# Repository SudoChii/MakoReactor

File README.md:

# Mako Reactor

CAD-as-code for layered leverless ("hitbox" style) fight controllers.

Describe where the buttons go, and Mako Reactor gives you back a stack of flat
plates you can send to a laser cutter, router, or 3D printer.

```python
import makoreactor as mr
from affine import Affine
from cadquery import exporters

layout = mr.FgcLeverless()
layout.layout_affine = Affine.translation(0, -13)

stack = mr.f1CapMako1.set(
    width=mr.in2mm(11.8),
    height=mr.in2mm(5),
    hole_deltax=300,
    layout=layout,
)

for i, plate in enumerate(stack.generate()):
    exporters.export(plate.edges(">Z"), f"layer{i}.dxf")
```

Or from a shell:

```bash
python -m makoreactor --layout fgc --width 11.8 --height 5 -o build/
```

## Install

Everything is available from conda-forge, so a single environment file covers it:

```bash
# replace mamba with conda if you don't have mamba
mamba env create -f environment.yml
mamba activate mako

pip install -e .
```

If you'd rather use pip alone, `pip install -e .` pulls `cadquery`, `numpy`, and
`affine` from PyPI; CadQuery ships the OpenCascade binaries as wheels.

Check it works:

```bash
pytest
```

## How it fits together

### Layouts (`makoreactor/layouts.py`)

A `Layout` holds button centres grouped by hand and function — `left_homerow`,
`right_homerow`, `left_thumb`, `right_thumb`, `misc` — and one affine per group
placing it on the plate. `layout_affine` shifts the whole cluster at once.

| layout | buttons | notes |
| --- | --- | --- |
| `CircleCapLeverless` | 20 | smash layout, Frame 1 circular caps |
| `Gccmx` | 22 | as above plus home/share, mimics Crane's GCCMX |
| `SquareCapLeverless` | 20 | smash layout, square MX keycaps |
| `Mako1Hadoe` | 20 | as above, right-hand eight dropped onto the home row |
| `WideGc` | 18 | as `Gccmx`, two thumb buttons a hand, no left pinky |
| `FgcLeverless` | 15 | traditional fighting-game layout, one thumb button |
| `SanwaFgcLeverless` | 15 | as above, spread out for 24/30mm Sanwa buttons |
| `FgcPlus` | 16 | as above on the smash spacing, pinky and two thumbs a hand, all 24mm |

The eight action buttons sit in two rows 22mm apart. In the smash layouts the
*bottom* row lines up with the four directionals, so the fingers rest low and
reach up; `Mako1Hadoe` drops the whole cluster by that one row pitch so the
*top* row lands on the home row instead.

`WideGc` keeps the smash spacing and the right hand's eight, and changes the
other three groups. The stock thumbs are lopsided — two buttons on the left, a
five-button c-stick on the right — so it cuts the right cluster back to its
bottom two, the same pair the left thumb already has, and both thumbs end up
with the same reach. The centre is Crane's, inherited from `Gccmx`: a row of
three on a 20mm pitch where the stock layout has one button. The left hand
loses its pinky — the outermost of its four, the same button `FgcLeverless`
drops — leaving three directionals. Eighteen buttons.

Dropping the pinky leaves the cluster 13mm right of the plate centre, since
nothing came off the right hand. Shift it back with
`layout.layout_affine = Affine.translation(-13.3, 0)` if that matters for the
plate you are cutting.

`layout.layout` is the flat list of centres in plate coordinates;
`layout.geom` is the same thing as cap outlines ready to cut.

### Parts (`makoreactor/parts/layered_leverless.py`)

Each part is a rounded rectangle with mounting holes, plus whatever it cuts:

| part | cuts |
| --- | --- |
| `Base` | nothing — solid bottom |
| `WireSpaceModelU` | interior frame for wiring, plus the USB-C breakout pocket |
| `Switchplate` | 14x14 switch mounts on every button centre |
| `F1CapFaceplate` | circular cap openings |
| `KeycapFaceplate` | square keycap openings |
| `Backplate` | cap openings, cosmetic top |
| `BrookWireSpace` | as `WireSpaceModelU`, deep enough to hang a Brook board in |
| `BrookSwitchplate` | as `Switchplate`, plus four board screws and a relief window |

Mounting holes are nested rectangles inset from the edge by `hole_offset`, each
one `hole_deltax` narrower than the last, until another would not fit. A 13.5"
plate at the default 275mm pitch gets eight holes; an 11.8" plate at 300mm gets
the four corners.

`WireSpaceModelU` carries the USB-C opening. Going inwards from the plate edge:
a `usbc_slot_width` slot the connector pokes through, then a
`usbc_pocket_width` x `usbc_pocket_depth` pocket that the small breakout PCB
sits in, with a `usbc_relief_radius` semicircle either side of it — tangent to
the pocket walls and centred on its top edge — so the board can be seated and
levered back out. Below that, `usbc_throat_width` runs the wires down into the
cavity between the two arms of the boss.

#### Housing a Brook board (`brookMako1`)

`brookMako1` is the same five layers with two of them swapped, for a build that
carries a Brook Gen-5X/UFB rather than ModelU boards alone. The board hangs
face-up under the switchplate on standoffs, and everything else follows from
that:

```python
stack = mr.brookMako1                  # WideGc layout, 14x6", two 1/4" spacers
for ok, why in stack.checks():
    print("ok " if ok else "BAD", why)
```

`BrookWireSpace` needs no new cutout — the layer is already an open frame — so
what it adds is *depth*. Plates come from sheet, so depth only arrives in whole
thicknesses of stock: `spacers()` rounds the board up to a whole number of 1/4"
layers and `part_depth()` never returns less, whatever `n_modelu` says. The
board then sits as low as it goes, and `standoff_length()` is the rest of the
depth — the standoffs to actually buy. At the defaults that is two spacers,
12.70mm, and 8.10mm standoffs.

Whatever the components reach above that has to go somewhere, which is
`BrookSwitchplate`. It cuts four screw holes on the board's mounting pattern
and a window over the middle of the board — the PCB outline pulled in by
`board_rim`, so a rim of material is left all the way round carrying those four
screws. The window goes clean through, because these plates are cut flat and
there is no such thing as a pocket here. At the defaults the components stand
2.90mm proud of the switchplate's underside and the plate is 3.175mm thick, so
the faceplate closes over them untouched. Three spacers instead of two would
swallow the board whole and the window could come off (`board_relief=False`).

`checks()` measures all of that, plus the things that depend on where the board
sits: clearance to the nearest switch mount, to the corner screws, to the cavity
wall and the corner pads, and that each of the four screws lands on material
rather than in a switch mount. `check()` raises instead, and the CLI runs it
before writing anything:

```bash
python -m makoreactor --stack brook -o build/
```

Swap the layout and the checks are what notice. `--layout fgc` puts the FGC
layout's action buttons straight through the board, and the run stops with
`BAD: board clears the nearest switch mount by -24.5mm` rather than cutting it.

**Two numbers here are assumptions, not datasheet.** Brook publishes neither the
mounting hole pattern nor a height, so `BrookBoard` assumes holes 3.5mm in from
each corner — an 89.01 x 38.01mm pattern, the same assumption
`SanwaBody.board_hole_inset` already made, with a test pinning the two together
— and an 11mm tallest component. Measure your board before cutting; both are
fields, and `component_height` is the one that decides whether the faceplate
stays closed.

### Sanwa parts (`makoreactor/parts/sanwa_fgc.py`)

The same idea built out of arcade parts instead of mechanical switches. Snap-in
buttons need a panel 2–3.9mm thick to grip, but a 320mm plate that thin flexes,
and a rear panel, a board mount and screw bosses are not flat — so the stack
splits into three cut plates and one printed body:

| part | is | carries |
| --- | --- | --- |
| `SanwaTopPlate` | 3mm, cut | the button holes, 24mm and 30mm |
| `SanwaSupportPlate` | 6mm, cut | the same holes 4mm wider; stiffens the top plate |
| `SanwaBody` | 36mm, printed in two | walls, rear panel, board holder, skirt, screw bosses |
| `SanwaBottomPlate` | 3mm, cut | closes the bottom |

Two stacks ship: `sanwaFgc` on the FGC layout (320 x 200mm) and `sanwaFgcPlus`
on `FgcPlus` (460 x 215mm), which puts the hands 200mm apart as the smash
layouts do and rests both of them on the same row.

`FgcPlus` is arranged around the **top** row of the right-hand eight being the
home row, where the fingers rest:

* the left hand gets four buttons — the mirror of the right hand's second row,
  pinky included — carried up one `row_pitch` so it lands level with the right
  hand's *top* row. Both hands rest at the same height.
* the thumbs sit exactly where the smash layouts put MX and MY — just inboard
  of the index finger and well below it — and stay there when the hands go up,
  so the reach is longer here than on those layouts: 87mm below the index
  button against Mako1's 69mm.
* the three menu buttons are off the face — they are on the back panel, and
  hanging them off one corner stopped the cluster centring. Put them back with
  `layout.misc_coords = FgcLeverless.misc_coords`.

The board sits under the right palm, outboard of the thumb cluster. That corner
is what sets the width: with the thumbs at MX/MY they take the inboard half of
it, and the cluster is centred, so the room has to come from both sides.

#### How it goes together

Nothing threads into plastic and nothing is glued. The printed body takes brass
**M3 heat-set inserts** — a 4.2mm hole 6mm deep, the standard seat for a
4.6 × 5.7mm insert — pressed in with a soldering iron before anything else
happens. Every screw is then an M3 machine screw into brass, and every insert
goes in from the face its screw comes from, so all of them are reachable on a
bare printed half.

`fasteners()` prints the schedule for whatever the stack is currently set to:

```
22 x M3 heat-set inserts, 4.2mm hole x 6mm deep
14 x M3 x 14 screws, down through both top plates into the body
 8 x M3 x 8 screws, up through the bottom plate
 4 x M3 x 8 self-tapping screws, up into the board standoffs
 2 x 4mm dowels x 10mm, locating the printed halves
```

Then, in order: dowel the two halves together, press the rear buttons and the
jack into the back panel, screw the board up into its standoffs from
underneath, snap the face buttons into the top plate and wire them, lay the
support plate on the body and the top plate on that, and run the long screws
down through both into the rim. The bottom plate goes on last, from below, and
is the only thing to take off to get at the board again.

#### Where the screws go

The rim pattern follows the chamfered outline in: **one screw per chamfer**
rather than one either side of it, then as many along each straight edge as it
takes to keep the spacing under `screw_pitch`. The top two plates pick up two
more over the board holder, so the middle of the span is fastened as well as
the edge.

The bottom plate does not repeat all of that. Nothing pushes on it and it
carries no buttons, so it takes a **subset** of the rim — the four corners plus
enough of the rest to keep its own spacing under `bottom_screw_pitch`. Every
screw it skips is a heat-set insert saved too. Between that and the single
corner screws, a `sanwaFgc` went from 32 fasteners to 22.

**The outline** is a rectangle with the corners chamfered off rather than
rounded, and both ends of every chamfer rounded — `corner_chamfer` and
`corner_fillet`. The cavity follows it in, so the wall stays an even thickness
the whole way round.

**The board hangs from the top of the cavity**, not off the floor: an 8mm slab
under the lid, the Brook on standoffs below it, and that same slab taking the
two middle screws. Pulling the bottom plate gets you at the board without
touching the button plates.

**The skirt** is a flange turned inwards round the bottom of the walls,
`skirt_width` deep into the cavity. The body is open underneath, which leaves
the printed halves floppy and the bottom plate spanning unsupported; the skirt
ties the walls together, carries the plate all the way round, and gives the
print a wide flat face. Its opening repeats the outline's treatment at a larger
scale — a chamfered rectangle with the chamfers rounded — and has to stay big
enough to pass the board through, since the board goes in from underneath.

**The back wall** puts the USB-C jack on the centreline in the Neutrik D-series
footprint (24mm bore, two M3 screws diagonally opposite it), with 24mm OBSF-24
buttons divided evenly either side — two and two by default,
`rear_button_count=6` for three a side, and the pitch closes up on its own so
the outermost button still lands on the straight part of the wall. Nothing back
there is bigger than a 24mm button; the 30mm one is the face thumb button, and
it is a 36mm wall. Neither a snap-in button nor the jack will fit that wall, so
it is relieved from the inside to `rear_panel_thickness` around each of them.

Each rear button gets a **release slot** either side of it, `tab_slot_width` x
`tab_slot_height`, running right up to the hole. A snap-in button's tabs are
behind the panel they grip, and once the case is shut there is no other way to
reach them; with the slots you can pinch the tabs through the wall and push the
button back out. The bezel covers most of each slot. They widen what a rear
button asks of the wall, so the screw and split placement works around them
too.

Where the screws can go along that edge is decided by what is mounted in it: a
button's body reaches 24.5mm past the wall, so a boss behind one would be inside
it. `rear_screw_points()` drops one into each bay between components wide enough
to take it, and leaves the ends to the side edges.

**The body prints in two pieces.** It does not fit a bed whole, so `halves()`
cuts it down `split_x()` — not down the middle, where the jack is, but through
the clear bay beside it. That position is derived from the rear panel rather
than fixed, so moving the buttons moves the split instead of stranding it in
one of them; `split_offset` pins it if you want. The halves locate on dowels
through the front and back walls and are clamped by the plates that screw into
both. `sanwaFgc` comes off a 220 x 220mm bed; `sanwaFgcPlus` is bigger and
wants 250 x 250.

Almost every dimension here is pinned by another one, so the assembly states
those constraints as checks rather than leaving them in a comment:

```python
for ok, why in mr.sanwaFgcPlus.checks():
    print("ok " if ok else "BAD", why)
```

`check()` raises instead, and both the CLI and the tests run it. It is what
caught the failures this design walked into: a rear button whose body passes
through a screw boss, a jack tucked under the corner where the misc buttons hang
down into the same space, a plate too shallow to keep rear button bodies clear
of the row in front of them — which is why it is 200mm deep rather than the
170mm the button layout alone needs — four corner screws left hanging in the air
once the corners were chamfered, and a board holder wide enough to reach a wall
only by cutting through the thumb cluster on the way.

```bash
python -m makoreactor --stack sanwa -o build/   # plates as DXF, body halves as STEP
```

### Sharing parameters

`LayeredAssembly.set(**kwargs)` pushes shared parameters into every layer that
accepts them and returns a new assembly, so stacks are cheap to fork:

```python
wide = mr.f1CapMako1.set(width=mr.in2mm(13.5), hole_deltax=275)
```

`generate()` returns the plates in stack order; `assemble()` returns a CadQuery
`Assembly` with them stacked along Z.

## Reference exports

`notebooks/mako1_fgc/layer{0..4}.dxf` were cut from real material and are
treated as the specification. `tests/test_reference_export.py` regenerates them
and compares outlines, mounting holes, button openings, and fillet arcs.

The parts module was never committed to this repo — it was reconstructed from
those exports, the notebook that produced them, and the earlier
`makogen/parts.py` in the git history. All five layers now regenerate exactly:
every entity count, every hole, and every arc matches to the hundredth of a
millimetre.

## Notebook and rendering

`notebooks/demo.ipynb` walks through layouts, building a stack, rendering it,
exporting DXFs, and a Pi Pico holder.

```bash
jupyter lab notebooks/demo.ipynb
```

Its `show()` helper prefers [jupyter-cadquery][jcq] for interactive OCP
rendering and falls back to a flat inline SVG when the viewer is missing or no
Jupyter server is reachable — so the notebook still runs headless under
nbconvert or nbclient.

[jcq]: https://github.com/bernhard-42/jupyter-cadquery

To get the 3-D viewer, use the environment that pins a matching OCP:

```bash
mamba env create -f environment-viewer.yml
mamba activate mako-viewer
pip install -e ".[viewer]"
```

jupyter-cadquery 4.0.2 targets OCP 7.8, which is what CadQuery 2.7 pins, so that
environment holds CadQuery one minor version back and resolves cleanly. If you
are already on CadQuery 2.8 (OCP 7.9), the viewer works there too, but you need
newer tessellation than jupyter-cadquery asks for — `pip` will report the pin
conflict, and it is safe to ignore:

```bash
pip install jupyter-cadquery
pip install --upgrade ocp-tessellate ocp-vscode
```

`LayeredAssembly.assemble()` is built for this: it stacks the layers along Z and
colours them so they can be told apart. Pass `explode=True` to load the viewer's
explode tool, then drag the animation slider under the render to pull the plates
apart and check that cutouts line up between layers.

```python
show(stack.assemble(), explode=True)
```

The explode distance is fixed at 2.5x by the viewer itself — three-cad-viewer's
`explode(duration=2, speed=1, scale=2.5)` is called with no arguments, and
jupyter-cadquery's `explode` is only a boolean that switches the tool on. If you
need the plates further apart, `assemble(gap=...)` spaces them in the model
instead, which also works without the viewer.

To send renders to a docked side panel instead of the cell output, call
`open_viewer("Mako", anchor="right")` once.

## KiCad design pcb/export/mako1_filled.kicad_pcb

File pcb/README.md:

# Mako1 switch PCB

The board that goes where the switchplate goes: same outline, same bolt
pattern, 20 key switches on the layout's own centres, everything else hanging
underneath in the space `WireSpaceModelU` already opens up.

Written in [atopile](https://github.com/atopile/atopile) — the circuit is a
`.ato` file, the footprints and the placement are generated from the same
numbers the plates are cut from.

```bash
python tools/build_parts.py             # footprints and symbols -> parts/
ato build                               # netlist + footprints
python tools/place.py --format json > tools/placement.json
python tools/place_pcb.py               # put them where the layout says
python tools/place.py --format check    # does the layout still fit
python tools/place.py --format stack    # does the board still fit the stack
```

`ato build` gives you the right parts and the right nets, but it stacks them in
a row at the origin — the placement is the second half of the job, and
`place_pcb.py` is what does it: every switch on its layout centre, the Pico and
the Model UD flipped to the back, the outline and the eight bolt holes drawn on
Edge.Cuts. Run it after any `ato build`; it sets absolute positions, so running
it twice changes nothing.

### If the board looks like everything is in a line

That is a board that has been built but not placed, and it is what both the
atopile 3D view and the layout viewer in VS Code will show you, faithfully:
every footprint sitting at the origin 10mm apart, and no board outline — which
is also why `kicad-cli` starts warning `Board outline is malformed`. Both
symptoms are the one cause.

atopile owns the netlist and the footprints; nothing in the `.ato` file says
where a part goes, and 0.15.8 has no placement trait and no post-build hook to
hang one on. So a build that starts from a layout it cannot match writes the
default row, and the placement is gone.

The extension makes this easy to hit: it watches the project and rebuilds on
its own when a file changes. So run the two together rather than separately —

```bash
tools/build.sh            # ato build, then place, then check
tools/build.sh --export   # ...and write the fab files
```

It finds its own tools, because none of the three is on PATH and two of them
are easy to get wrong — plain `python` finds miniforge's *base* environment,
which has no cadquery in it, so the script tests each candidate by trying to
import `makoreactor` rather than trusting the name. Override any of them if
your paths differ:

```bash
ATO=/path/to/ato PY=/path/to/python KICAD_CLI=/path/to/kicad-cli tools/build.sh
```

— and if the viewer ever shows the row again, `python tools/place_pcb.py` puts
it back. It sets absolute positions, so it is safe to run at any time, and a
plain `ato build` afterwards keeps them.

### Why the placement does not go through pcbnew

It edits the `.kicad_pcb` as text rather than driving KiCad's Python, and that
is deliberate. **KiCad 10 rewrites a board it saves**: it drops the net table
and writes pad nets by name only — `(net "gnd")` where atopile expects
`(net 12 "gnd")`. atopile 0.15.8 cannot read that back, so one save from
pcbnew ends the round trip and the next `ato build` fails on its own layout
file. Editing the text in place keeps the file in the dialect both tools read.

Opening the board in KiCad is fine. Saving it there is a one-way door: after
that, re-run `ato build` from a clean `layout/` if you need the netlist
regenerated.

### Installing the CLI

atopile is **not on conda-forge** — it is PyPI only, and every release since
0.14.1006 needs **Python 3.14**, so it cannot go in the `mako` environment
(3.11). It wants its own:

```bash
conda create -n ato -c conda-forge python=3.14
conda activate ato
pip install atopile
```

Two things to know about the CLI. It prints `0.15.8 is the last CLI release and
is in maintenance mode only` on every run — atopile has moved to the editor
extension and app.atopile.io for 0.16+, so this project is pinned to a CLI that
will not get fixes. And `ato validate` is broken in 0.15.8
(`ImportError: cannot import name 'front_end'`); `ato build` works, which is
what matters here.

## Where the wiring comes from

None of it is invented. Two sources, both worth reading before changing
anything:

**[The Model UD wiring diagram](https://github.com/HTangl/Model-UD)** (in its
`Pictures/` folder) gives the breakout-to-Pico connections, and this board
makes all of them:

| Model UD | Pico | why |
| --- | --- | --- |
| GND | GND | — |
| VSYS | VSYS | through the breakout's own Schottky |
| 5V | VBUS | raw bus voltage |
| GCD | GP28 | GameCube detect — without it the board is USB only |
| D+ / D− | TP3 / TP2 | by wire; the Pico has no header pins for these |

The diagram also says *connect AGND to GND*, which this does. The pads are
named as the board silkscreens them — `GCD`, `D-`, `D+`, `GND`, `3V`, `VSYS`,
`5V`.

**[HayBox](https://github.com/JonnyHaystack/HayBox)** `config/pico/config.cpp`
gives the button pinout, and this board uses it verbatim — LF1-4 on GP2-5,
RF1-8 on GP26/21/19/17/27/22/20/18, LT1-2 on GP6-7, RT1-5 on
GP14/15/13/12/16, MB1 on GP0, and GP28 as `joybus_data`. HayBox names buttons
by position rather than by function, which is exactly how the layout groups
them, so the mapping is one-to-one and a board built to it runs stock firmware
with no config edit. `place.py --format check` fails if the pinout drifts from
that list.

## What is on it

| | |
| --- | --- |
| 20 key switches | Choc v1 hotswap or soldered; MX soldered |
| Raspberry Pi Pico | on the back, on headers or soldered flat |
| Model UD / BirdD | on the back, USB-C |
| bolt holes | the stack's own eight, nothing added |

Direct wired: one GPIO per switch, common ground, no matrix and no diodes.
GP2040-CE turns on the RP2040's internal pull-ups, so that is the entire
circuit — which is why the interesting part of this project is the footprint
and the placement rather than the schematic.

## The switch footprint

One footprint takes either standard, because the low profile switches this
board is built around are not the only ones people have in a drawer:

| | Kailh Choc v1 | Cherry MX (and MX-pinned low profile) |
| --- | --- | --- |
| hotswap socket | yes, CPG135001S30 on the back | no |
| soldered direct | yes | yes |

**MX cannot be hotswapped here.** Its socket wants 3mm holes at the MX pin
positions, and those overlap the Choc socket's — 2.67 and 2.77mm apart, when
each needs 3mm. One standard or the other gets the sockets, and since the
brief was low profile by default, Choc gets them.

Getting both standards into one footprint at all comes down to which holes
share a net. MX pin 2 lands 2.67mm from Choc pin 1, closer than any two
pieces of copper on different nets could be, so the poles are paired to put
those two on the *same* net, where they are allowed to overlap. What is left
between opposite poles is **0.173mm**, at the Choc pin 2 / MX pin 2 pair.
That is above a 2-layer fab's 0.127mm floor and below anything comfortable, so
`tools/build_parts.py` recomputes it on every run and refuses to write a
footprint that closes it further.

## Pinout

GP2040-CE's stock Pico mapping, so the board runs on stock firmware without a
config. Switch numbers are layout order — the same order `mako1.ato` declares
them and `tools/place.py` places them.

| SW | GPIO | GP2040-CE | | SW | GPIO | GP2040-CE |
| --- | --- | --- | --- | --- | --- | --- |
| 1 | GP4 | Right | | 11 | GP8 | R2 |
| 2 | GP3 | Down | | 12 | GP20 | A1 |
| 3 | GP5 | Left | | 13 | GP2 | Up |
| 4 | GP13 | L1 | | 14 | GP21 | A2 |
| 5 | GP10 | B3 | | 15 | GP19 | R3 |
| 6 | GP11 | B4 | | 16 | GP18 | L3 |
| 7 | GP12 | R1 | | 17 | GP16 | S1 |
| 8 | GP9 | L2 | | 18 | GP14 | spare |
| 9 | GP6 | B1 | | 19 | GP15 | spare |
| 10 | GP7 | B2 | | 20 | GP17 | S2 / start |

GP14 and GP15 are the two c-stick positions this layout has and GP2040-CE's
default mapping does not; assign them in the web configurator.

## USB needs two wires

The Pico's D+ and D- do not come out on its 40-pin header — they are only on
the TP2/TP3 pads underneath it. So the Model UD's pair stops at a labelled
link beside the Pico footprint, and you run two short wires to those pads.
Every DIY Pico controller does this; there is no way to do it in copper alone
short of reflowing the Pico flat and trusting its test pads to land, which is
not a thing to ask of a hand-built board.

Power does not need wires: the Model UD's VSYS pin is VBUS through its own
Schottky, which is exactly what the Pico's VSYS wants, so it is a track.

## Fitting the stack

The switchplate it replaces is 3.175mm; a PCB is 1.6mm. **The stack loses
1.575mm** unless you make it up — either 1.6mm of spacer under the faceplate,
or order the board at 3.2mm, or let the keycaps sit that much lower, which
with low profile switches may be what you want anyway. Nothing in the layered
parts changes; `Switchplate` simply is not cut.

`tools/place.py` reports the clearances that matter on the current layout:

```
closest two switch footprints: +2.95mm
closest switch to a bolt hole: +9.91mm
closest switch to the board edge: +8.67mm
```

## What is checked, and what is not

**It builds.** `ato build` runs clean through every stage — instance graph,
electrical design, PCB update, post-PCB checks and all the report targets — and
writes `layout/default/default.kicad_pcb` with 22 footprints on it: 20
`MakoKeySwitch`, one Pico, one Model UD, designated SW1-SW20, U1 and J1.

The netlist has been read back out of that PCB and checked against the source:
all 20 switch A poles land on the GPIO `mako1.ato` names them to, all 20 B
poles share one net, and the Pico and Model UD agree on `gnd` and `vsys`. Nets
are named by function — `sw_right`, `sw_b1`, `usb_dp` — so the board reads
without cross-referencing.

Four things the first build turned up, in case they help elsewhere: trait
arguments cannot span lines; footprints must be the modern `(footprint ...)`
s-expression, not the legacy `(module ...)`; designators are only handed to
parts carrying `has_part_picked`, so a custom part needs it even though nothing
is being picked; and `override_net_name` only takes on a concrete package pin
(`pico.package.GND`), not on a locally declared interface, where the stdlib's
own `hv`/`lv` suggestions win.

**DRC is clean.** `kicad-cli pcb drc` reports 0 violations on the placed board
(KiCad 10.0.5). The 105 unconnected items it also reports are the nets: there
are no traces yet — `ato build` and `place_pcb.py` give you parts, nets and
placement, and routing is still yours to do.

Three things DRC caught that the earlier hand checks had missed, all now fixed:

- The switch footprint was drawn at the **19.05mm key pitch instead of the
  15.6mm switch body**, so on a layout whose thumb cluster sits at 18.5mm every
  one of those footprints overlapped its neighbour.
- `fits()` measured the straight-line distance between switch centres, which is
  the wrong measure for two axis-aligned squares — it read +2.95mm on a pair
  that overlapped by a millimetre. It measures the box gap now.
- The MX pin pad at 1.9mm came within 0.173mm of the Choc socket pad beside it,
  under the 0.2mm a 2-layer fab holds. At 1.8mm it clears by 0.223mm, with
  0.15mm of annular ring left.

The symbols are minimal hand-rolled `.kicad_sym` files, enough to carry pin
names.

## Exports

```bash
kicad-cli pcb export gerbers --output export/gerbers layout/default/default.kicad_pcb
kicad-cli pcb export drill   --output export/gerbers/ layout/default/default.kicad_pcb
kicad-cli pcb export dxf     --output export/outline --layers Edge.Cuts --output-units mm ...
kicad-cli pcb export step    --output export/mako1_pcb.step ...
```

The DXF and the STEP are the ones that answer *does it fit*, and they have been
checked against the plate rather than eyeballed: the exported outline is
**355.60 x 152.40mm** against the switchplate's 355.60 x 152.40, and its eight
bolt holes land on the plate's own pattern at 10mm. The STEP imports into
cadquery beside the rest of the stack.

Note `--output-units mm`: kicad-cli writes DXF in inches by default, which is
how an outline that is exactly right shows up as "14.00 x 6.00".

### The one thing that does not fit

`python tools/place.py --format stack` spells it out: the PCB is **1.6mm where
the switchplate was 3.175mm**, so there is 1.575mm to make up in the stack.

1.6mm is the right number, not a compromise — an MX or Choc switch clips into a
1.5mm plate, and that is what a board of this thickness gives it. The plate it
replaces was 1/8in because it was acrylic and had to be stiff on its own. So
either shim the difference, or set `Switchplate(depth=1.6)` and let the stack
come out 1.575mm shorter.

Everything that hangs underneath fits the 12.7mm wire space: the Pico soldered
flat is 2.4mm, on headers 11.0mm, the Model UD 5.0mm, and Choc sockets 1.85mm.
The Pico on headers is what wants `n_modelu=2` rather than 1.

The footprint geometry is checked, and against real sources: Cherry MX and
Kailh Choc drawings, cross-referenced with
[daprice/keyswitches.pretty](https://github.com/daprice/keyswitches.pretty)
(CC BY-SA 4.0), and the Model UD dimensions measured out of the Model BirdD
KiCad files in [HTangl/Model-UD](https://github.com/HTangl/Model-UD). Before
ordering, diff `parts/MakoKeySwitch/MakoKeySwitch.kicad_mod` against a
footprint from a library you trust — 0.173mm is not the place to find out a
number was off.

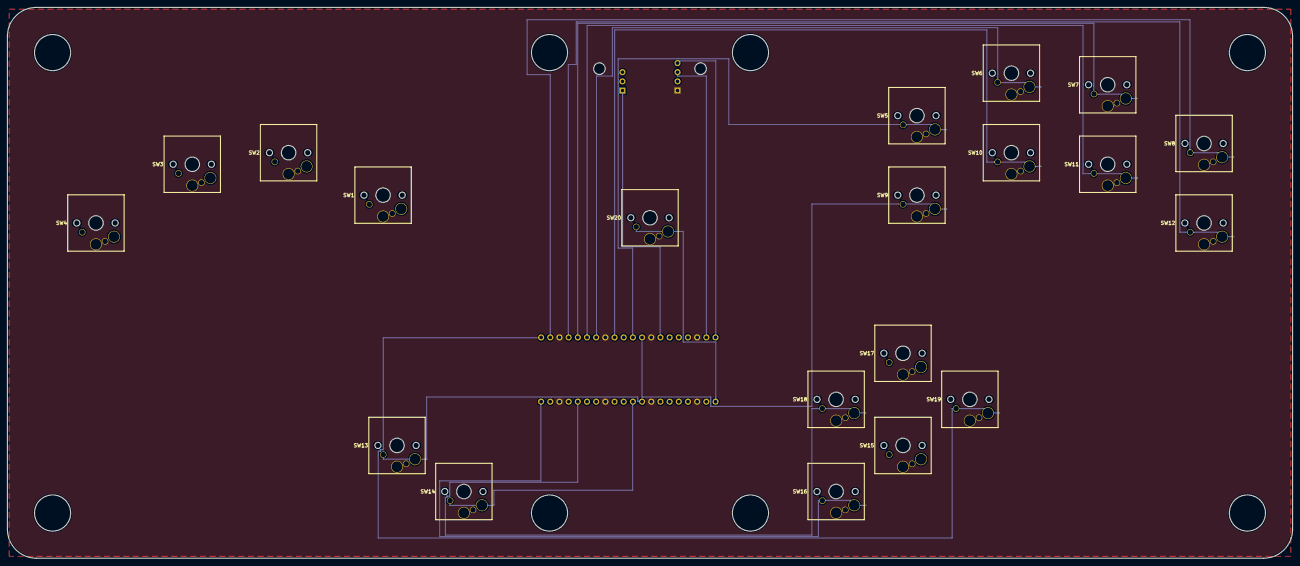
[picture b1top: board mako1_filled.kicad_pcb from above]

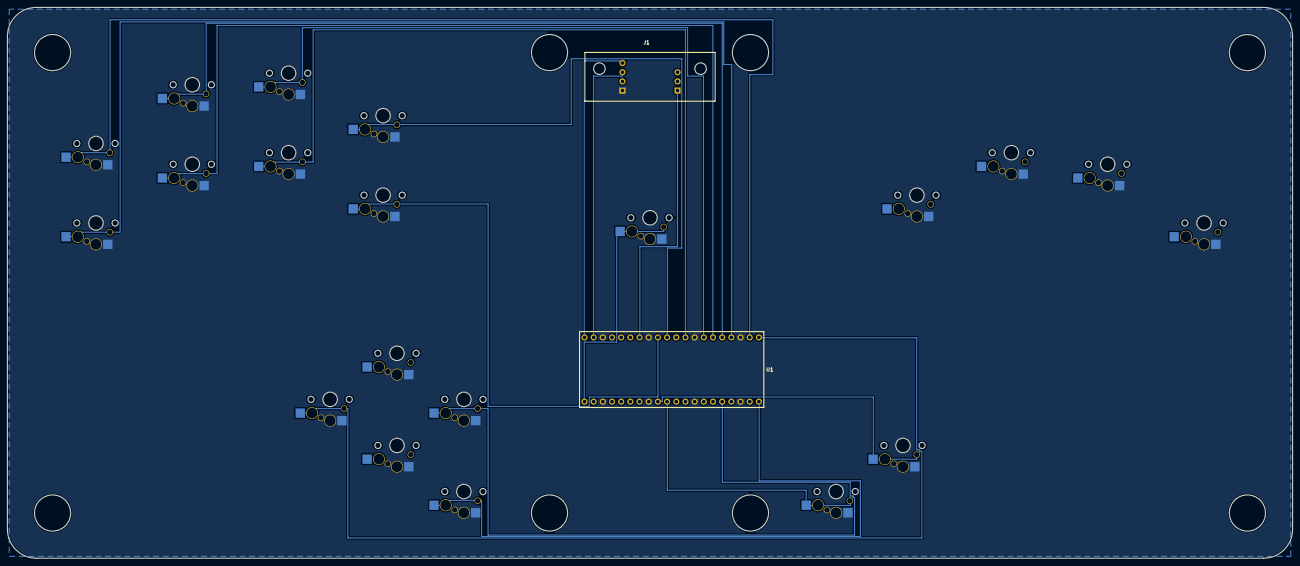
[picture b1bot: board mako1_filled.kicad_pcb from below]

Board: 2 copper layers, 355.6 x 152.4 mm, 22 parts (2 on the bottom side), 24 nets.

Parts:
J1: ModelUD
SW1, SW2, SW3, SW4, SW5, SW6, SW7, SW8, SW9, SW10, SW11, SW12, SW13, SW14, SW15, SW16, SW17, SW18, SW19, SW20: MakoKeySwitch
U1: RaspberryPiPico

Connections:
gnd: J1.GND, SW1.B, SW2.B, SW3.B, SW4.B, SW5.B, SW6.B, SW7.B, SW8.B, SW9.B, SW10.B, SW11.B, SW12.B, SW13.B, SW14.B, SW15.B, SW16.B, SW17.B, SW18.B, SW19.B, SW20.B, U1.AGND, U1.GND
joybus: J1.GCD, U1.GP28
sw_lf1: SW1.A, U1.GP2
sw_lf2: SW2.A, U1.GP3
sw_lf3: SW3.A, U1.GP4
sw_lf4: SW4.A, U1.GP5
sw_lt1: SW13.A, U1.GP6
sw_lt2: SW14.A, U1.GP7
sw_mb1: SW20.A, U1.GP0
sw_rf1: SW5.A, U1.GP26
sw_rf2: SW6.A, U1.GP21
sw_rf3: SW7.A, U1.GP19
sw_rf4: SW8.A, U1.GP17
sw_rf5: SW9.A, U1.GP27
sw_rf6: SW10.A, U1.GP22
sw_rf7: SW11.A, U1.GP20
sw_rf8: SW12.A, U1.GP18
sw_rt1: SW15.A, U1.GP14
sw_rt2: SW16.A, U1.GP15
sw_rt3: SW17.A, U1.GP13
sw_rt4: SW18.A, U1.GP12
sw_rt5: SW19.A, U1.GP16
vbus: J1.V5, U1.VBUS
vsys: J1.VSYS, U1.VSYS
